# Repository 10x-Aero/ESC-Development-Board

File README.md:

https://github.com/user-attachments/assets/5f652ef7-dc9c-4700-bebd-08a81333550c

# ESC Development Board

A 6S AM32-compatible ESC built as a proof of concept for learning how to design an ESC from scratch. It gets a motor spinning — that's about the extent of what's guaranteed. Beyond that, expect rough edges.

The design is sloppy in places. If you spot schematic, layout, or component choices that actively work against basic ESC functionality, open an issue.

## Hardware

- **MCU:** STM32F051
- **Firmware:** AM32
- **Max cells:** 6S

### Schematic

### PCB layers

## Testing

### Setup

- **Motor:** AOS Supernova 3220 925KV
- **Battery:** 6S LiPo
- **Prop:** 7×7
- **Bulk cap:** 1000 µF
- **Measurement:** AC-coupled VBAT ripple, probed directly at the battery solder pads

### Throttle sequence

| t (s) | Action         | Throttle | Duration |
| ----- | -------------- | -------- | -------- |
| 0.0   | Idle           | —        | 1.0 s    |
| 1.0   | Ramp           | 0 → 20%  | 1.5 s    |
| 2.5   | Hold (capture) | 20%      | 2.0 s    |
| 4.5   | Ramp           | 20 → 35% | 0.8 s    |
| 5.3   | Hold (capture) | 35%      | 2.0 s    |
| 7.3   | Ramp           | 35 → 50% | 0.8 s    |
| 8.1   | Hold (capture) | 50%      | 2.0 s    |
| 10.1  | Ramp           | 50 → 65% | 0.8 s    |
| 10.9  | Hold (capture) | 65%      | 2.0 s    |
| 12.9  | Ramp           | 65 → 80% | 0.8 s    |
| 13.7  | Hold (capture) | 80%      | 2.0 s    |
| 15.7  | Ramp           | 80 → 95% | 0.8 s    |
| 16.5  | Hold (capture) | 95%      | 2.0 s    |
| 18.5  | Ramp down      | 95 → 0%  | 1.5 s    |
| 20.0  | End            | —        | —        |

### Results

https://github.com/user-attachments/assets/3ce99b9d-343a-43b4-ace9-065e4792fe87

## Known mistakes

- The DRV8300DPWR has internal bootstrap diodes, so the external bootstrap diodes on this design are redundant. Doesn't break anything — just unnecessary parts cost and board area.

## Flashing AM32 on a custom ESC

General workflow for getting AM32 running on any custom STM32-based ESC, not just this one. Two things to figure out for your own board: which AM32 target matches your pin layout, and how to physically flash it.

### Figuring out the pin config

AM32 organizes pin assignments in two layers:

- **Hardware groups** define the low-level pins — signal input, the six phase outputs (three high-side PWM + three low-side COM), BEMF feedback pins, and the comparator reference. Grouped per MCU family (`F0_A`, `F0_B`, etc.) and listed in the [AM32 Supported Hardware wiki](https://github.com/AlkaMotors/AM32-MultiRotor-ESC-firmware/wiki/List-of-Supported-Hardware).
- **Targets** sit on top of a hardware group and add ADC pins for voltage and current sensing, plus anything board-specific like LED pins. Target definitions live in `Inc/targets.h` in the [am32-firmware/AM32 repo](https://github.com/am32-firmware/AM32) as `#ifdef` blocks.

Compare your schematic against the hardware group table. If one matches your phase outputs, BEMF pins, and signal input exactly, use it and write a target that points to your ADC pins. If nothing matches, you'll need to define a new hardware group — that means editing the MCU-level source, not just a target header.

Match your signal input pin carefully. The bootloader `.hex` filename encodes which pin it expects (e.g. `..._PB4_V17.hex` expects the signal on PB4). Mismatches mean the ESC won't respond to the configurator.

### Flashing the bootloader

SWD only — the bootloader has to go on over ST-Link. Wire SWDIO, SWCLK, and GND from the ST-Link to the SWD pads on the ESC, and power the ESC from a LiPo.

1. Install [ST-LINK Utility](https://www.st.com/en/development-tools/stsw-link004.html).
2. Grab the correct bootloader from [am32.ca/downloads](https://am32.ca/downloads).
3. Flash the `.hex` to `0x08000000`.

### Flashing the firmware

Once the bootloader is on, the main firmware goes over the signal wire via FC passthrough — no more SWD needed.

1. Connect the ESC's signal and GND to a flight controller motor output, and plug the FC into your PC via USB.
2. Install the [AM32 Offline Configurator](https://github.com/am32-firmware/Offline-Configurator/releases).
3. Download the firmware `.hex` matching your target from the [AM32 releases](https://github.com/am32-firmware/AM32/releases).
4. Open the configurator, connect to the FC's serial port, and flash the `.hex`.

The FC needs to be running a DShot protocol (300 or 600) for passthrough to work, and the ESC needs battery power — USB alone won't boot it.

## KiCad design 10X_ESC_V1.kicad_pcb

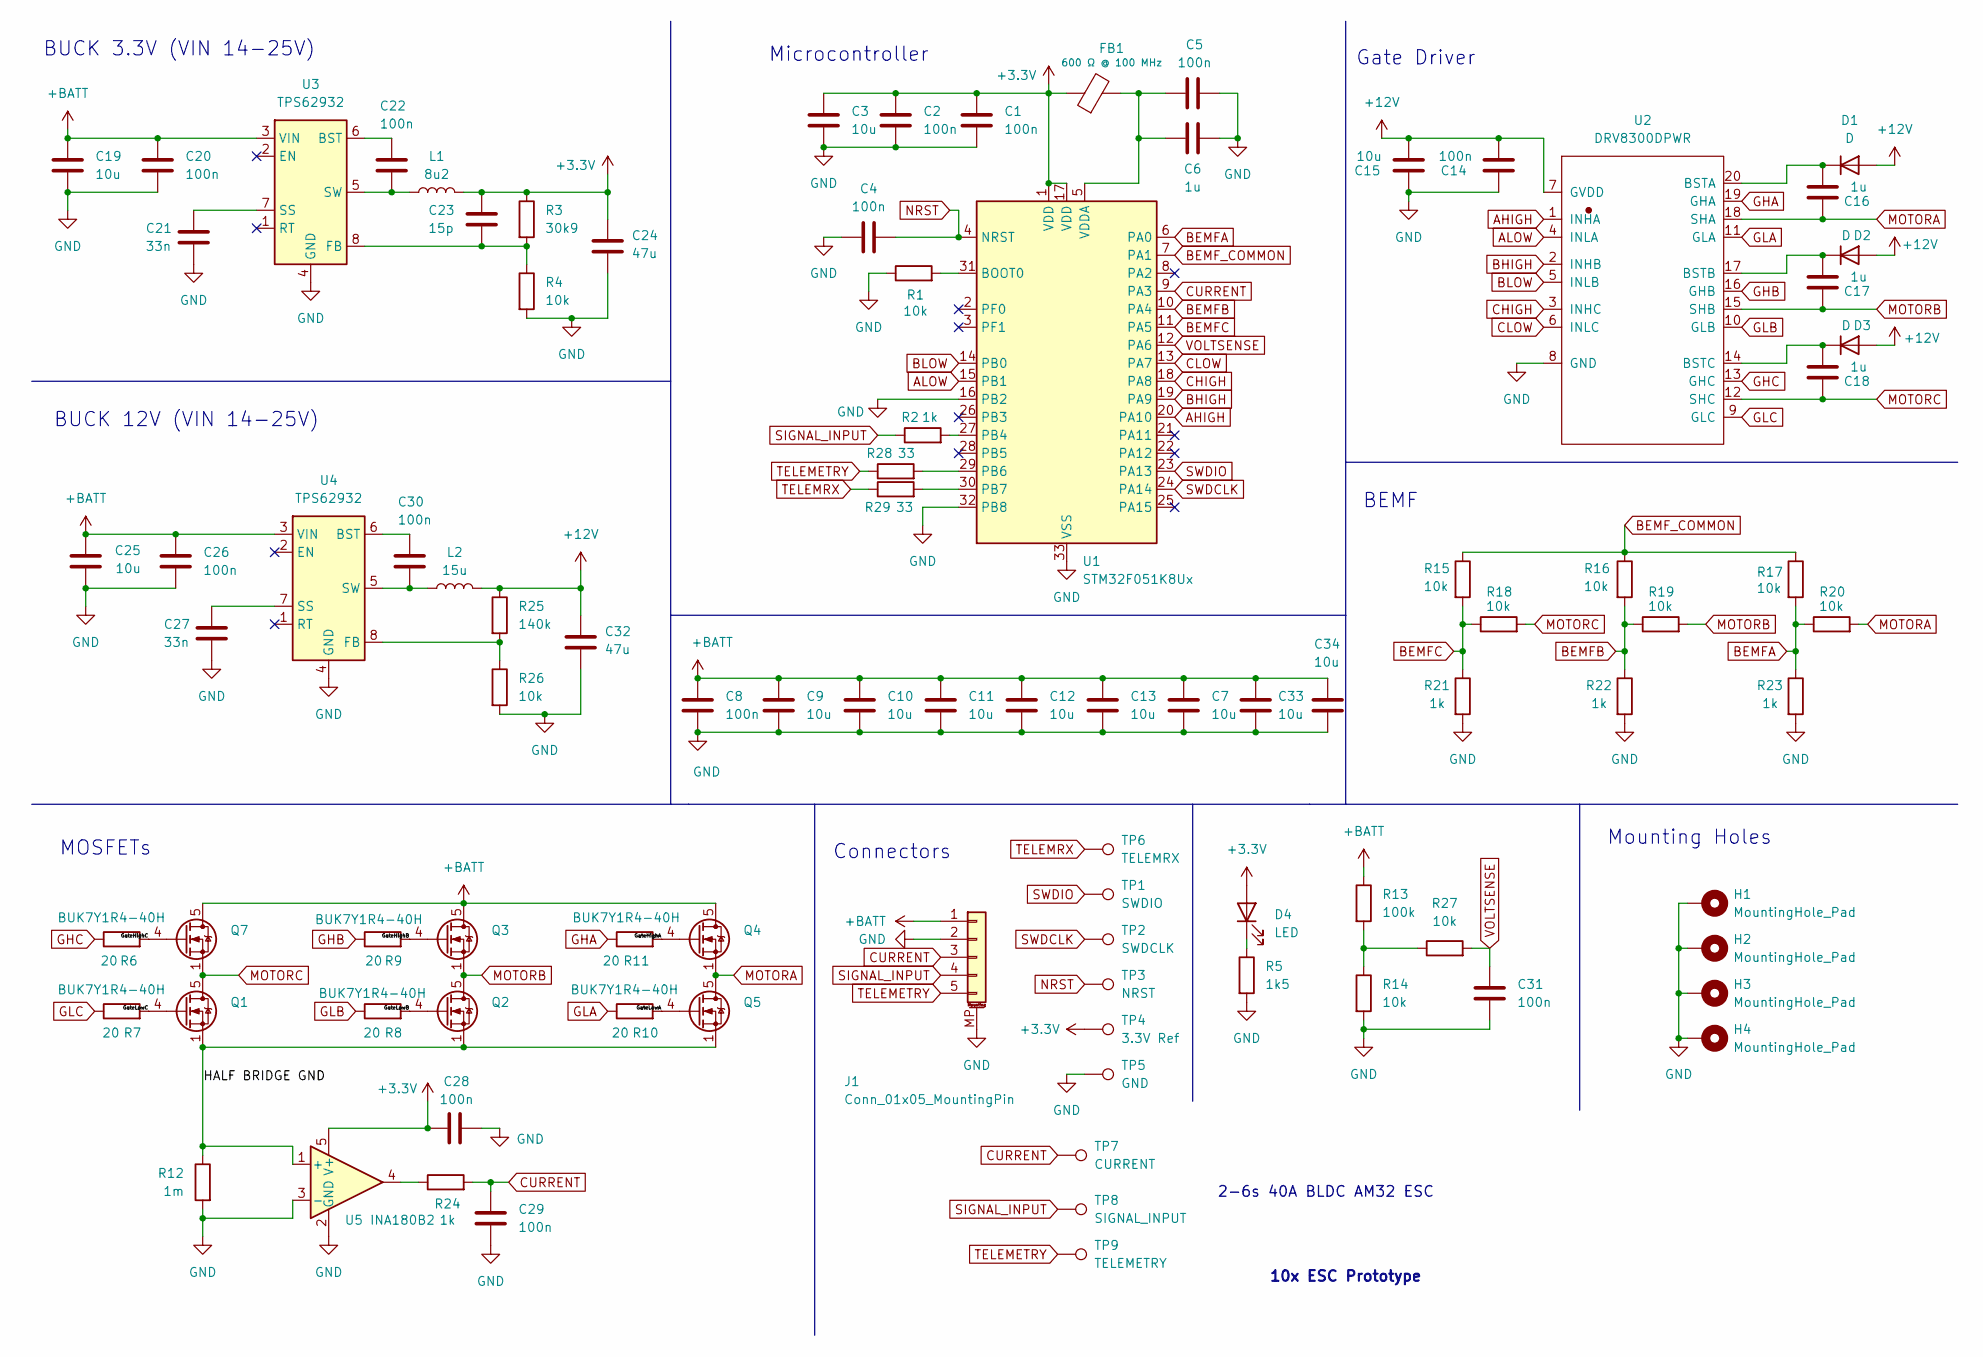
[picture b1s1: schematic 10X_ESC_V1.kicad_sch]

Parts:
C1, C2, C4, C5, C14, C22, C28, C29, C30, C31: 100n; C_0402_1005Metric; Manufacturer Part Number CA0522618; LCSC Part # C307331
C3, C15: 10u; C_0603_1608Metric; LCSC Part # C96446
C6: 1u; C_0402_1005Metric; LCSC Part # C52923
C7, C9, C10, C11, C12, C13, C33, C34: 10u; C_1210_3225Metric; LCSC Part # C53084452
C8: 100n; C_1210_3225Metric; LCSC Part # C2179722
C16, C17, C18: 1u; C_0603_1608Metric; LCSC Part # C15849
C19, C25: 10u; C_0805_2012Metric; LCSC Part # C440198
C20, C26: 100n; C_0603_1608Metric; LCSC Part # C14663
C21, C27: 33n; C_0402_1005Metric; LCSC Part # C106862
C23: 15p; C_0402_1005Metric; LCSC Part # C1548
C24, C32: 47u; C_1210_3225Metric; LCSC Part # C77101
D1, D2, D3: D; D_SMA; LCSC Part # C2480
D4: LED; LED_0603_1608Metric; LCSC Part # C111340
FB1: 600 Ω @ 100 MHz; L_0603_1608Metric; LCSC Part # C85833
H1, H2, H3, H4: MountingHole_Pad; Flightcontroller_MountingHolePad_M4
J1: Conn_01x05_MountingPin; JST_GH_SM05B-GHS-TB_1x05-1MP_P1.25mm_Horizontal; LCSC Part # C189896
L1: 8u2; L_KOHERelec_MDA7030; LCSC Part # C436550
L2: 15u; L_KOHERelec_MDA7030; LCSC Part # C2847486
Q1, Q2, Q3, Q4, Q5, Q7: BUK7Y1R4-40H; LFPAK56; LCSC Part # C6423721
R1, R4, R14, R15, R16, R17, R18, R19, R20, R26, R27: 10k; R_0402_1005Metric; LCSC Part # C25744
R2, R21, R22, R23, R24: 1k; R_0402_1005Metric; LCSC Part # C11702
R3: 30k9; R_0402_1005Metric; LCSC Part # C270615
R5: 1k5; R_0402_1005Metric; LCSC Part # C25867
R6, R7, R8, R9, R10, R11: 20; R_0402_1005Metric; LCSC Part # C25089
R12: 1m; R2725; LCSC Part # C469381
R13: 100k; R_0402_1005Metric; LCSC Part # C25741
R25: 140k; R_0402_1005Metric; LCSC Part # C114151
R28, R29: 33; R_0402_1005Metric; LCSC Part # C25105
TP1: SWDIO; Flightcontroller_Solder_Pad
TP2: SWDCLK; Flightcontroller_Solder_Pad
TP3: NRST; Flightcontroller_Solder_Pad
TP4: 3.3V Ref; Flightcontroller_Solder_Pad
TP5: GND; Flightcontroller_Solder_Pad
TP6: TELEMRX; Flightcontroller_Solder_Pad
TP7: CURRENT; Flightcontroller_Solder_Pad
TP8: SIGNAL_INPUT; Flightcontroller_Solder_Pad
TP9: TELEMETRY; Flightcontroller_Solder_Pad
U1: STM32F051K8Ux; QFN-32-1EP_5x5mm_P0.5mm_EP3.45x3.45mm; LCSC Part # C72339
U2: DRV8300DPWR; TSSOP-20_L6.5-W4.4-P0.65-LS6.4-BL; LCSC Part # C3036056
U3, U4: TPS62932; SOT-583-8; LCSC Part # C3032935
U5: INA180B2; SOT-23-5; LCSC Part # C2861539

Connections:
+3.3V: C1.1, C2.1, C3.1, C23.1, C24.1, C28.1, D4.2 (A), FB1.1, L1.2, R3.1, TP4.1, U1.1 (VDD), U1.17 (VDD), U5.5 (V+)
+12V: C14.2, C15.2, C32.1, D1.2 (A), D2.2 (A), D3.2 (A), L2.2, R25.1, U2.7 (GVDD)
+BATT: C7.1, C8.1, C9.1, C10.1, C11.1, C12.1, C13.1, C19.1, C20.1, C25.1, C26.1, C33.1, C34.1, J1.1, Q3.5 (D), Q4.5 (D), Q7.5 (D), R13.1, U3.3 (VIN), U4.3 (VIN)
/GateHighA: Q4.4 (G), R11.2
/GateHighB: Q3.4 (G), R9.2
/GateHighC: Q7.4 (G), R6.2
/GateLowA: Q5.4 (G), R10.2
/GateLowB: Q2.4 (G), R8.2
/GateLowC: Q1.4 (G), R7.2
/HALF BRIDGE GND: Q1.1 (S), Q1.2 (S), Q1.3 (S), Q2.1 (S), Q2.2 (S), Q2.3 (S), Q5.1 (S), Q5.2 (S), Q5.3 (S), R12.1, U5.1 (+)
AHIGH: U1.20 (PA10), U2.1 (INHA)
ALOW: U1.15 (PB1), U2.4 (INLA)
BEMFA: R17.2, R20.1, R23.1, U1.6 (PA0)
BEMFB: R16.2, R19.1, R22.1, U1.10 (PA4)
BEMFC: R15.2, R18.1, R21.1, U1.11 (PA5)
BEMF_COMMON: R15.1, R16.1, R17.1, U1.7 (PA1)
BHIGH: U1.19 (PA9), U2.2 (INHB)
BLOW: U1.14 (PB0), U2.5 (INLB)
CHIGH: U1.18 (PA8), U2.3 (INHC)
CLOW: U1.13 (PA7), U2.6 (INLC)
CURRENT: C29.1, J1.3, R24.2, TP7.1, U1.9 (PA3)
GHA: R11.1, U2.19 (GHA)
GHB: R9.1, U2.16 (GHB)
GHC: R6.1, U2.13 (GHC)
GLA: R10.1, U2.11 (GLA)
GLB: R8.1, U2.10 (GLB)
GLC: R7.1, U2.9 (GLC)
GND: C1.2, C2.2, C3.2, C4.1, C5.2, C6.2, C7.2, C8.2, C9.2, C10.2, C11.2, C12.2, C13.2, C14.1, C15.1, C19.2, C20.2, C21.2, C24.2, C25.2, C26.2, C27.2, C28.2, C29.2, C31.2, C32.2, C33.2, C34.2, H1.1, H2.1, H3.1, H4.1, J1.2, J1.MP (MountPin), R1.1, R4.2, R5.2, R12.2, R14.2, R21.2, R22.2, R23.2, R26.2, TP5.1, U1.16 (PB2), U1.32 (PB8), U1.33 (VSS), U2.8 (GND), U3.4 (GND), U4.4 (GND), U5.2 (GND), U5.3 (-)
MOTORA: C16.1, Q4.1 (S), Q4.2 (S), Q4.3 (S), Q5.5 (D), R20.2, U2.18 (SHA)
MOTORB: C17.1, Q2.5 (D), Q3.1 (S), Q3.2 (S), Q3.3 (S), R19.2, U2.15 (SHB)
MOTORC: C18.1, Q1.5 (D), Q7.1 (S), Q7.2 (S), Q7.3 (S), R18.2, U2.12 (SHC)
NRST: C4.2, TP3.1, U1.4 (NRST)
unnamed: C16.2, D1.1 (K), U2.20 (BSTA)
unnamed: C17.2, D2.1 (K), U2.17 (BSTB)
unnamed: C18.2, D3.1 (K), U2.14 (BSTC)
unnamed: D4.1 (K), R5.1
unnamed: R13.2, R14.1, R27.1
unnamed: R24.1, U5.4
unnamed: R1.2, U1.31 (BOOT0)
unnamed: R2.2, U1.27 (PB4)
unnamed: R28.2, U1.29 (PB6)
unnamed: R29.2, U1.30 (PB7)
unnamed: C5.1, C6.1, FB1.2, U1.5 (VDDA)
unnamed: C22.1, U3.6 (BST)
unnamed: C23.2, R3.2, R4.1, U3.8 (FB)
unnamed: C21.1, U3.7 (SS)
unnamed: C22.2, L1.1, U3.5 (SW)
unnamed: C30.1, U4.6 (BST)
unnamed: R25.2, R26.1, U4.8 (FB)
unnamed: C27.1, U4.7 (SS)
unnamed: C30.2, L2.1, U4.5 (SW)
SIGNAL_INPUT: J1.4, R2.1, TP8.1
SWDCLK: TP2.1, U1.24 (PA14)
SWDIO: TP1.1, U1.23 (PA13)
TELEMETRY: J1.5, R28.1, TP9.1
TELEMRX: R29.1, TP6.1
VOLTSENSE: C31.1, R27.2, U1.12 (PA6)

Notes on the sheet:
2-6s 40A BLDC AM32 ESC
BEMF
MOSFETs
Gate Driver
BUCK 3.3V (VIN 14-25V)
Mounting Holes
10x ESC Prototype
BUCK 12V (VIN 14-25V)
Microcontroller
Connectors

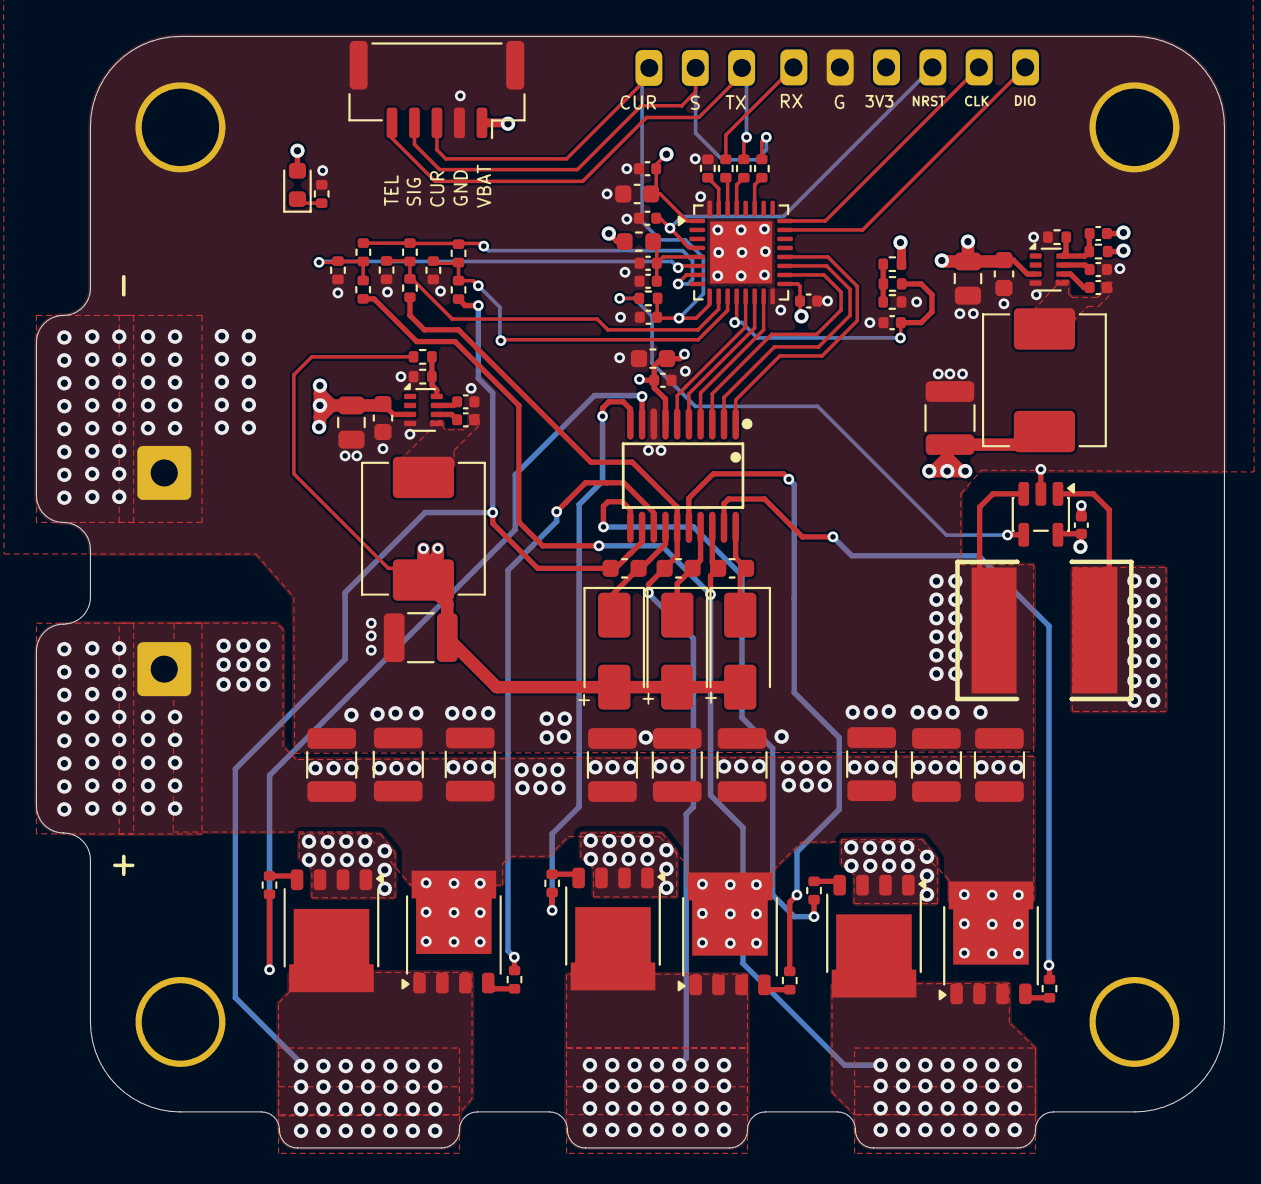
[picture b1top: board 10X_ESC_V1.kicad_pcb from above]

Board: 4 copper layers, 66.0 x 61.8 mm, 95 parts (0 on the bottom side), 57 nets.

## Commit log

2026-04-21 Initial
2026-04-21 edit readme
2026-04-21 upload images for readme
2026-05-07 Add images for VBAT ripple at different throttle levels
2026-05-07 update screenshot filenames
2026-05-07 Update README with additional resource links
    Added links to external resources in the README.
